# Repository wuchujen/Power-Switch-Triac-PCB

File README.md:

# Power-Switch-Triac-PCB
PCB for Vintage Power Switch. Reduce current going to through the switch.

Created in KiCad

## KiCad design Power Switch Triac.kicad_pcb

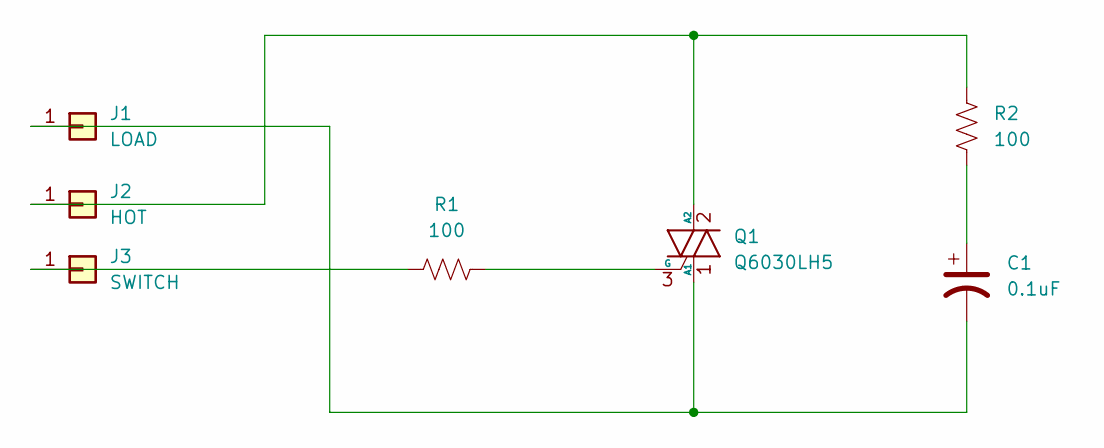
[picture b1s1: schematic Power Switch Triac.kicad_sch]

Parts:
C1: 0.1uF; C_Disc_D7.5mm_W4.4mm_P5.00mm
J1: LOAD; SolderWire-1.5sqmm_1x01_D1.7mm_OD3.9mm
J2: HOT; SolderWire-1.5sqmm_1x01_D1.7mm_OD3mm
J3: SWITCH; SolderWire-1.5sqmm_1x01_D1.7mm_OD3mm
Q1: Q6030LH5; TO-220-3_Vertical
R1, R2: 100; R_Axial_DIN0207_L6.3mm_D2.5mm_P10.16mm_Horizontal

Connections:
unnamed: C1.1, R2.2
unnamed: C1.2, J1.1, Q1.1 (A1)
unnamed: J2.1, Q1.2 (A2), R2.1
unnamed: Q1.3 (G), R1.2
unnamed: J3.1, R1.1

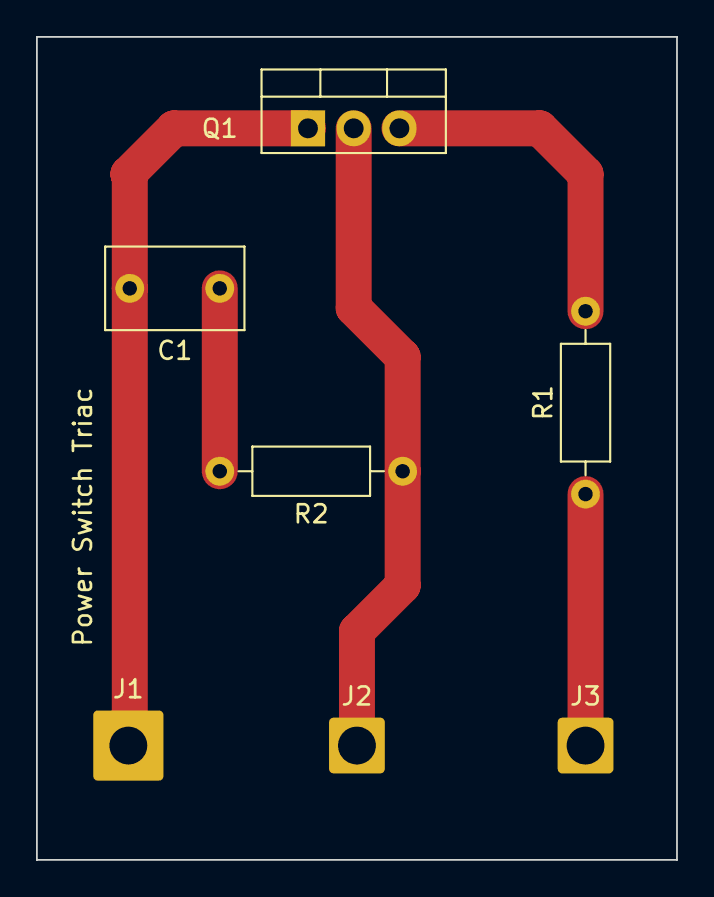
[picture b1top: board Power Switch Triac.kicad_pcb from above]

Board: 2 copper layers, 35.6 x 45.7 mm, 7 parts (0 on the bottom side), 5 nets.
